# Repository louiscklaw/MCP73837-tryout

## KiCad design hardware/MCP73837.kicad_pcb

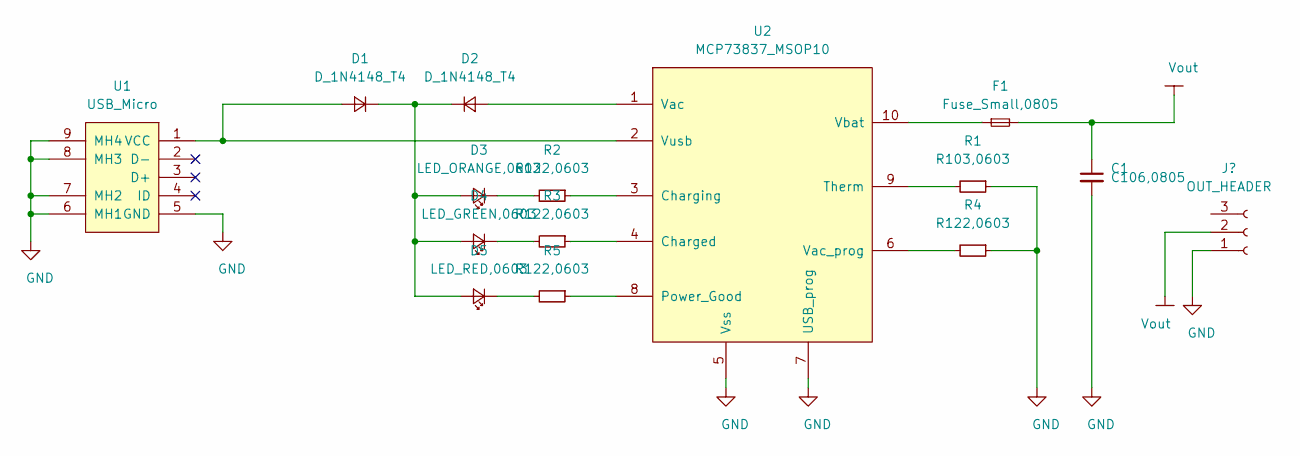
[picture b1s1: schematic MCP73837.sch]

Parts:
C1: C106,0805; C_0805_2012Metric_Pad1.15x1.40mm_HandSolder
D1, D2: D_1N4148_T4; D_SOD-123
D3: LED_ORANGE,0603; LED_0603_1608Metric
D4: LED_GREEN,0603; LED_0603_1608Metric
D5: LED_RED,0603; LED_0603_1608Metric
F1: Fuse_Small,0805; R_0805_2012Metric_Pad1.15x1.40mm_HandSolder
R1: R103,0603; R_0603_1608Metric_Pad1.05x0.95mm_HandSolder
R2, R3, R4, R5: R122,0603; R_0603_1608Metric_Pad1.05x0.95mm_HandSolder
U1: USB_Micro; USB_Micro-B_Molex-105017-0001
U2: MCP73837_MSOP10

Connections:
GND: C1.2, R1.1, R4.1, U1.5 (GND), U1.6 (MH1), U1.7 (MH2), U1.8 (MH3), U1.9 (MH4), U2.5 (Vss), U2.7 (USB_prog)
unnamed: D1.1 (K), D2.1 (K), D3.2 (A), D4.2 (A), D5.2 (A)
unnamed: D1.2 (A), U1.1 (VCC), U2.2 (Vusb)
unnamed: D2.2 (A), U2.1 (Vac)
unnamed: D3.1 (K), R2.2
unnamed: D4.1 (K), R3.2
unnamed: D5.1 (K), R5.2
unnamed: F1.1, U2.10 (Vbat)
unnamed: R1.2, U2.9 (Therm)
unnamed: R2.1, U2.3 (Charging)
unnamed: R3.1, U2.4 (Charged)
unnamed: R4.2, U2.6 (Vac_prog)
unnamed: R5.1, U2.8 (Power_Good)
Vout: C1.1, F1.2

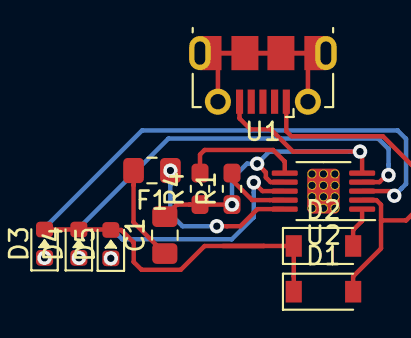
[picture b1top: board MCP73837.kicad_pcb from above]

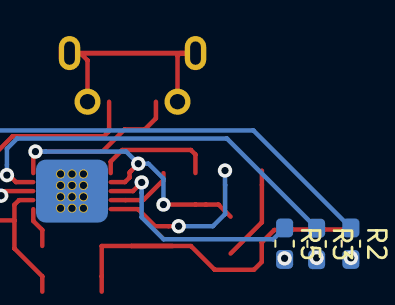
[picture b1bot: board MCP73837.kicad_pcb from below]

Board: 2 copper layers, 14 parts (3 on the bottom side), 14 nets.

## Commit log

2019-06-03 update,
2019-06-16 update filename,
2020-05-05 ci: init travis token,
2020-05-05 ci: init travis build config,
